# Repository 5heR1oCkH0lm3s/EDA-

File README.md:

# MyEDA — 数字电路原理图编辑器

“工业软件创新训练 I”四人课程项目，使用 C++17、wxWidgets 3.2 和 CMake。

在画布上放置逻辑门、连接引脚，点击开关验证 0/1 逻辑，保存工程或导出文件到 KiCad。

## 快速开始（Windows）

先安装 Visual Studio 2022 的“使用 C++ 的桌面开发”（含 CMake 工具），准备 wxWidgets 3.2 的 x64 静态库。首次配置见[新人上手指南](docs/使用指南/新人上手指南.md)。

| 你想做什么 | 仓库根目录中的入口 |
|---|---|
| 首次编译，或验证自己修改的代码 | 双击 `build.bat`，编译和测试通过后打开 `MyEDA/build/Debug/MyEDA.exe` |
| 更新当前分支并运行 | 先关闭 MyEDA，再双击 `update-and-run.bat` |
| 不更新，只运行已有程序 | 双击 `run.bat` |

更新入口要求工作区干净且当前分支有远程跟踪分支；有本地修改、拉取失败、编译失败或测试失败时停止。它不会自动提交、暂存或覆盖改动。Git 只更新源码，程序仍需编译；入口会自动完成增量编译。

打开示例：程序中选择“文件 → 打开”，选择 `examples/half_adder/half_adder.eda`，按 F5 后点击开关。

## 功能与范围

- 6 种逻辑门、开关、指示灯，共 8 种内置元件；支持用真值表定义双输入、单输出元件。
- 放置、移动、连线、框选、复制粘贴、删除、撤销和重做。
- 0/1 组合逻辑仿真，导线按逻辑值着色，指示灯显示输出。
- `.eda` 工程存档；KiCad 网表导入/导出；KiCad 原理图导出。

支持顶层时钟源和 D 触发器的步进仿真；当前没有模拟电压电流或器件延迟仿真。KiCad 样例展示封装和网络导入，尚未完成 PCB 布线；默认封装用于对接演示，不能直接视为可制造电路。详细限制见[操作手册](docs/使用指南/功能操作手册.md)。

完整分类索引见 [docs/README.md](docs/README.md)，示例说明见 [examples/README.md](examples/README.md)。

## 文档导航

| 目的 | 文档 |
|---|---|
| 安装、运行、排查启动错误 | [新人上手指南](docs/使用指南/新人上手指南.md) |
| 四人分支、提交、更新和合并 | [四人协作指南](docs/开发协作/四人协作指南.md) |
| 菜单、鼠标操作、快捷键与文件格式 | [功能操作手册](docs/使用指南/功能操作手册.md) |
| 理解代码和仿真原理 | [实现讲解](docs/开发协作/实现讲解-新手版.md) |
| 四人分工与期末贡献报告 | [四人分工与贡献说明](docs/课程资料/四人分工与贡献说明.md) |
| 分工和答辩演示 | [分工与答辩手册](docs/课程资料/分工与答辩手册.md) |
| 组织课程报告 | [课程报告写作指南](docs/课程资料/课程报告写作指南.md) |
| 数字电路基础 | [学习笔记](docs/学习笔记/) |
| 一页连续阅读 | [项目完整教程](docs/项目完整教程.md)（自动生成，请勿直接编辑） |

## 目录

```text
仓库根目录/
├── README.md                       项目介绍和入口导航
├── run.bat                         直接运行已编译程序
├── build.bat / build.ps1            编译本地代码并测试
├── update-and-run.bat / .ps1        更新、编译、测试并运行
├── MyEDA/
│   ├── src/                        程序源码和界面资源
│   ├── test/                       逻辑、文件与画布测试
│   ├── build/                      本机生成文件（不提交）
│   └── CMakeLists.txt
├── docs/
│   ├── README.md                   文档总索引
│   ├── 使用指南/                   安装运行、功能操作
│   ├── 开发协作/                   团队协作、实现讲解
│   ├── 课程资料/                   分工答辩、报告指南
│   ├── 学习笔记/                   数字电路基础
│   ├── images/                     截图、速查卡、上手图
│   └── 项目完整教程.md              自动生成的合集
├── examples/
│   ├── half_adder/                 半加器工程及 KiCad 文件
│   └── reference/                  KiCad 参考网表
└── tools/                          文档生成、图片生成和脚本检查
```

## 测试与文档维护

`build.bat` 会编译并运行测试；必须看到测试通过且脚本成功结束。逻辑与文件测试目前包含 64 项检查、子电路及合并兼容测试 53 项，画布测试另有 59 项，后续以实际输出为准。

以下命令在仓库根目录的 **PowerShell** 中执行。三种命令行工具模式：

```powershell
.\MyEDA\build\Debug\test_sim.exe --export-netlist .\examples\half_adder\half_adder.eda .\MyEDA\build\half_adder.net
.\MyEDA\build\Debug\test_sim.exe --export-kicad-sch .\examples\half_adder\half_adder.eda .\MyEDA\build\half_adder.kicad_sch
.\MyEDA\build\Debug\test_sim.exe --parse-netlist .\examples\half_adder\half_adder.net
```

修改 `docs/` 中源文档后，用 Python 3 更新并检查合集：

```powershell
python .\tools\merge_docs.py
python .\tools\merge_docs.py --check
```

Python 只用于维护文档，不是运行 MyEDA 的前置条件。演示图片和速查卡不会随文本自动更新，修改对应功能后需人工复核。

维护构建脚本时，可在成功编译一次后运行 `python .\tools\test_build_failure.py`：它在临时目录模拟测试编译失败，确认脚本不会运行遗留的旧测试。

## 子电路封装

支持把完整电路封装为多输入、多输出元件，并通过 `.edasub` 跨工程复用；演示工程见 `examples/subcircuits/`（从仓库根目录查找）。操作见[子电路封装指南](docs/使用指南/子电路封装指南.md)。

时序元件合并说明：支持顶层 D 触发器和时钟源，每 500ms 自动步进；D 触发器在上升沿采样。子电路封装目前用于组合逻辑，包含时钟或触发器的选区会提示暂不支持。

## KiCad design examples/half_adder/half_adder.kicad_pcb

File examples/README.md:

# 示例与参考文件

| 路径 | 用途 |
|---|---|
| [half_adder/half_adder.eda](half_adder/half_adder.eda) | 在 MyEDA 中打开半加器，按 F5 后点击开关仿真 |
| [half_adder/half_adder.net](half_adder/half_adder.net) | 导出的 KiCad 网表 |
| [half_adder/half_adder.kicad_sch](half_adder/half_adder.kicad_sch) | KiCad 原理图 |
| [half_adder/half_adder.kicad_pro](half_adder/half_adder.kicad_pro) | KiCad 工程 |
| [half_adder/half_adder.kicad_pcb](half_adder/half_adder.kicad_pcb) | KiCad 导入后的 PCB 样例（未完成布线） |
| [reference/kicad参考网表-真实导出.net](reference/kicad参考网表-真实导出.net) | KiCad 导出的参考网表，用于格式对照 |

在仓库根目录的 PowerShell 中打开样例：

```powershell
.\MyEDA\build\Debug\MyEDA.exe .\examples\half_adder\half_adder.eda
```

演示截图集中在 `docs/images/screenshots/`，与可编辑的工程样例分开保存。个人练习工程请另外保存，避免覆盖团队样例。

## 子电路封装

支持把完整电路封装为多输入、多输出元件，并通过 `.edasub` 跨工程复用；演示工程见 `examples/subcircuits/`（从仓库根目录查找）。操作见[子电路封装指南](../docs/使用指南/子电路封装指南.md)。

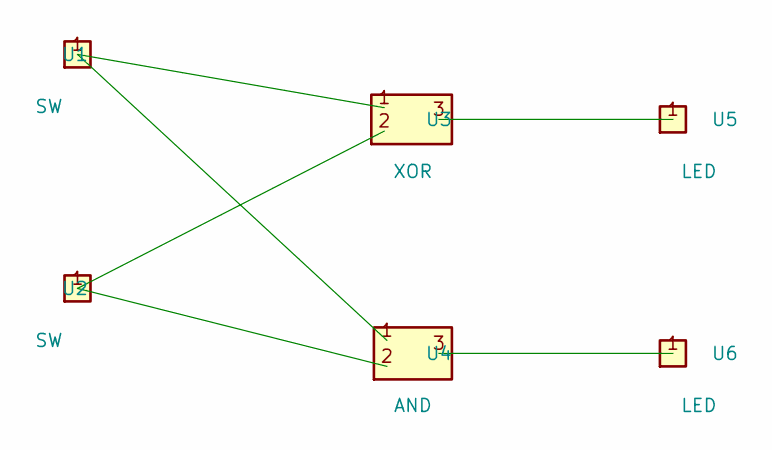
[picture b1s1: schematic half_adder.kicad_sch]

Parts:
U1, U2: SW
U3: XOR
U4: AND
U5, U6: LED

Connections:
unnamed: U1.1, U3.1, U4.1
unnamed: U2.1, U3.2, U4.2
unnamed: U3.3, U5.1
unnamed: U4.3, U6.1

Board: 2 copper layers, 6 parts (0 on the bottom side), 4 nets, no tracks yet.
